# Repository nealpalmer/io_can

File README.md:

# IO_CAN
CAN GPIO device (4 GPIO pins, input, output, PWM, NeoPixel, 4x ADC, 2x DAC, 5V out, 6-25V in, CAN 1Mb/s)

This is a circuit boards to plug into the FRC can bus, and give you 4 GPIO pins for use in software.  This should help reduce the complexity of wiring, by putting the GPIO near the device.  There is probably already CAN and power near where the sensor would need to be.

# todo:
- Finish schematics
- Finish firmware
- Finish FRC Java library

# Features:
- CAN interface to RoboRio (1Mbit, CAN-FD mode not supported)
- Pass-through CAN pins on 2 connectors
- Latching connector for CAN and GPIO.
- 4 GPIO pins (each connector has 5V,GND,GPIO,GPIO).
- digital input/output on all 4 pins
- 10-bit ADC input on all 4 pins
- 8-bit DAC+OPAMP output on 2 pins
- AB decoder on 2 pins
- Neopixel output on 1 pin.  Supports 6 LED groups, and each group is a programmable number of LEDs.
- PWM output on all 4 pins (TBD)???
- PWM input measurement on all 4 pins (TBD)???
- 5V @ 1A output power
- 6V to 25V input voltage (very low current draw, except for 5V output power)
- Reverse voltage protection on CAN and GPIO connectors.
- Can be powered by USB or CAN connector (but don't do both, because it might back-power the USB port).

# RGB led
- One led is for CAN informaion {green flashing = working, red flashing = no valid can detected, blue flashing = running in match}
- One led for status of GPIO[0,1] {xor 0&1, ADC->brightness, AB decoder lsb, DAC->brightness, direct software control}
- one led for status of GPIO[2,3] {...}

# CAN messages
- Set RGB leds
- Set pin mode&value {input, output 0/1, pwm width/period, pwm measure, ADC value, DAC, neopixel group/RGB, ab decoder}
- Status of GPIO {GPIO[0] 16-bit, GPIO[1] 16-bit, GPIO[2] 16-bit, GPIO[3] 16-bit}.
- status: AB decoder uses 32 bits.
- status: PWM decoder reports 16-bit floating point
  
# NeoPixel
- Uses an off-the-shelf neopixel array (WS2812B 5V leds) [Strip_of_leds](https://www.amazon.com/dp/B09PBHJG6G) [ring_of_leds](https://www.amazon.com/dp/B08GPWVD57)
- Takes over GPIO#0
- You MUST pay attention to the current draw of the string.  The entire IO_CAN is limited to 1A, and if you draw much more than that, the fuse will blow, and everything will stop working.  So make sure that the length of string can't draw too much power.
- Possibly add an external power connection to power the neopixel array.
- Color choices:
  - 0x00-0x3f: Black-to-White solid color choices (4 values per R,G,B)
  - 0x80-0xff: Single white LED on (can be set to match the rotary encoder)
  - Rainbow
  - Moving Rainbow

# Files included:
- UsbJoy_d12_a4_r-rev2/: Kicad layout files, and gerbers
- SmartButton-rev2/: Kicad layout files, and gerbers
- UsbJoy_bill_of_materials.csv: spreadsheets with all of the parts to purchase and quantities and ordering links, pcb, buttons, cables, other stuff...
- mechanics/: openscad & STL files for a couple of mounts for UsbJoy using the SmartButton, rotary dial, 
- software/SmartButton_firmware/:
- software/UsbJoy_firmware/: firmware for the Atmega32U4 microcontroller
- software/UsbJoy_pic_firmware/: firmware 
- software/program_pic/: small application to program the pic16f1778 on UsbJoy, and pic15f15213 on SmartButton

# Manufacturing suggestions:
- [oshpark.com](https://oshpark.com/) has wonderful pricing for qty3 of 2and4 layer boards and ships in 10 calendar days for almost everything (and you can pay more to get it earlier, or pay for faster shipping)
  - [UsbJoy_R2](https://oshpark.com/shared_projects/QPZCB1ZT) board order $20/3 boards
  - [SmartButton_R2](https://oshpark.com/shared_projects/OV1uAkH7) board order $1.70/3 boards ($6.80/12 boards)
- A 3d-printer can make the UsbJoy board attach directly to the screw threads of one of the buttons.  A couple of sample mount's source files are [here](https://makerworld.com/en/models/1602536-usbjoy-controller-mount-30mm-arcade-button).
- An 3d printed [encoder spring](https://makerworld.com/en/models/1602721-rotary-encoder-rotary-friction-spring) makes the encoder much better for not spinning the robot wildly.
- An [acrylic wheel](https://makerworld.com/en/models/1605249-encoder-finger-wheel) with finger holes for the encoder is very useful.
- Testing for button functionality can be done in windows with the built-in "USB game controllers"->properties window to see the buttons that get pressed. NEED A PICTURE HERE!
- You can extract a 3d model of the boards from kicad to use in your 3d cad system.  Kicad: File->Export->STEP
- digikey has all of the electrical components necessary (except for the LED and Arduino board).
- 3x UsbJoy parts kit
- 12x SmartButton parts kit
- The arduino pro micro has a 0.5A fuse on it.  The bottom side of the board will NOT be accessible.  If that 0.5A fuse is on the bottom side, and you have over current, then your boards will not be salvageable.  So get a version that has all the components on the top side.
- The discrete components are 0603 packages for easier soldering.
- Get some [illuminated magnifying glasses](https://www.amazon.com/YOCTOSUN-Magnifying-Rechargeable-1-5X-3-5X-Magnifier/dp/B0D8J3TYL3) for ease of soldering of small components. 
- Solder all of the SMT components before any thru-hole components.  Required for both boards, because some of the thru-hole soldering will make SMT parts unreachable.

# How to program Arduino Pro Micro's Atmega32U4 (the USB device):
- Run the [Arduino GUI](https://www.arduino.cc/en/software/) version 1.8.19 (or newer than May 2025).
- Load the *.ino file
- Set up the board to be "Arduino Leonardo".
- Plug in the board into USB, then select the right Com port in the Arduino GUI.
- "Upload" 
 from the Arduino GUI.
- Programming does not clear the EEPROM, so any settings should remain unaffected.

# How to program pic16f1778 on UsbJoy using PICKIT5 programmer:
- Disconnect the last 2 buttons (Yellow and white next to each other)
- type "q1" on the uart to disable the 7,10,11 button communications
- Run the [Microchip IDE](https://www.microchip.com/en-us/tools-resources/develop/mplab-x-ide)
- Load the project
- Compile the project for production
- Use one of the current PIC programmers (pickit5 is probably preferred), and plug it into the 5-pin holes on the bottom side of the board.  And have the IDE program the device.
- type "q0" on the uart to re-enable the last 2 button functionality
# How to program pic16f1778 on UsbJoy using UsbJoy's USB connection:
- Disconnect buttons 7,10,11 (Green, White, Yellow) - they will interfere with the programming.
- Connect UsbJoy to the Windows PC.
- Figure out what com port (use Windows Device Manager) UsbJoy is using.
- Run "program_pic.exe usbjoy [filename].hex COM[#]"
- Press and hold the button next to the rotary connector for the full programming time (about 15 seconds).  If you forget this step, then you will receive a message "Error: couldn't find expected PIC CPU".
- Wait for programming to complete.
- Release the button.
- You can now reconnect the disconnected buttons.

# How to program pic16f15213 on SmartButton using PICKIT5:
- Run the [Microchip IDE](https://www.microchip.com/en-us/tools-resources/develop/mplab-x-ide)
- Load the project
- Compile the project for production
- Make sure the SmartButton isn't pressed, Connect the 3-pin cable to the UsbJoy (for 5V power), plug the pickit5 into the 5-pin holes on the SmartButton board.  And have the IDE program the device.
# How to program pic16f15213 on SmartButton using UsbJoy's USB interface:
- Connect 3+3+3pin cable ends into UsbJoy (match yellow J12,white J11,green J8 connectors), connect 5-pin cable end into SmartButton.
- Run "program_pic sb smartbutton.hex COM[#]".
- Quick Test: While plugged into the 5-pin cable, you should see the led in the button flicker VERY VERY dim.
- Quick Test: While plugged into the 5-pin cable, if you press the button, the LED should light up.
- You will need to create a cable to connect J8,J11,J12 to a 5-pin header.  It is probably easiest and more reliable to make an 3+3+3-pin to 5-pin XH only cable, and then solder the B5B-XH header to a 0.1" header.
 - pin1: MCLRn -> Red/Green/J8.2
 - pin2: 5V -> White/White/J11.1
 - pin3: GND -> Blue/Yellow/J12.3
 - pin4: PGD -> Blue/Yellow/J12.2
 - pin5: PGC -> White/White/J11.2
 - 
 - 

# How to initially configure UsbJoy:
- Connect USB to a PC.
- Open a terminal program (I like [MobaXterm](https://mobaxterm.mobatek.net/)), and connect to the correct com port (use windows device manager, and find the 'leonardo' port listed) (linux: 'dmesg' to find the correct '/dev/ttyUSB#' when you plug into USB).
- Any baud rate is fine, because it is a virtual serial port.
- 'h'+enter to get the help menu
- All settings commands are "letter+hex_number+enter".
- Important EEPROM settings to run:
  - 'u#" to set the upper 4 bits for the virtual buttons to uniquely identify this particular board (saved to EEPROM)
  - "m#val" to set the SmartLed DEFAULT setting for that port (not for the SmartLed itself) to the desired LED pattern (and toggle functionality) (saved to EEPROM)
  - "n#" to set the number of neopixel leds in the string - set to "n0" to indicate that there isn't a neopixel string.
  - "v#" to set the power-on setting for the Green ports - probably want them always on "vF" unless they are being used in some interesting way.
  - "V#" to set the power-on DEFAULT for the Green ports (saved to EEPROM)

# Future enhancements
- Add a 5-pin direct programming header for connecting to SmartButton (no need for weird programming cable).
- Move QR code to top side of board.

# History of major changes
- 8/8/2025: Added RZ axis to have the full resolution of the 2400/rev encoder when used with FRC DriverStation that only has 200 values per axis.
- 7/16/2025: Added MPLAB project files.
- 7/16/2025: SmartButton pic programming working over USB
- 7/16/2025: Added PDF of schematics.
- 7/15/2025: Uploaded 3d and lasercut objects to makerworld.com

Neal Palmer,
**FRC team #2984 Vikings Robotics,**
La Jolla, CA, USA

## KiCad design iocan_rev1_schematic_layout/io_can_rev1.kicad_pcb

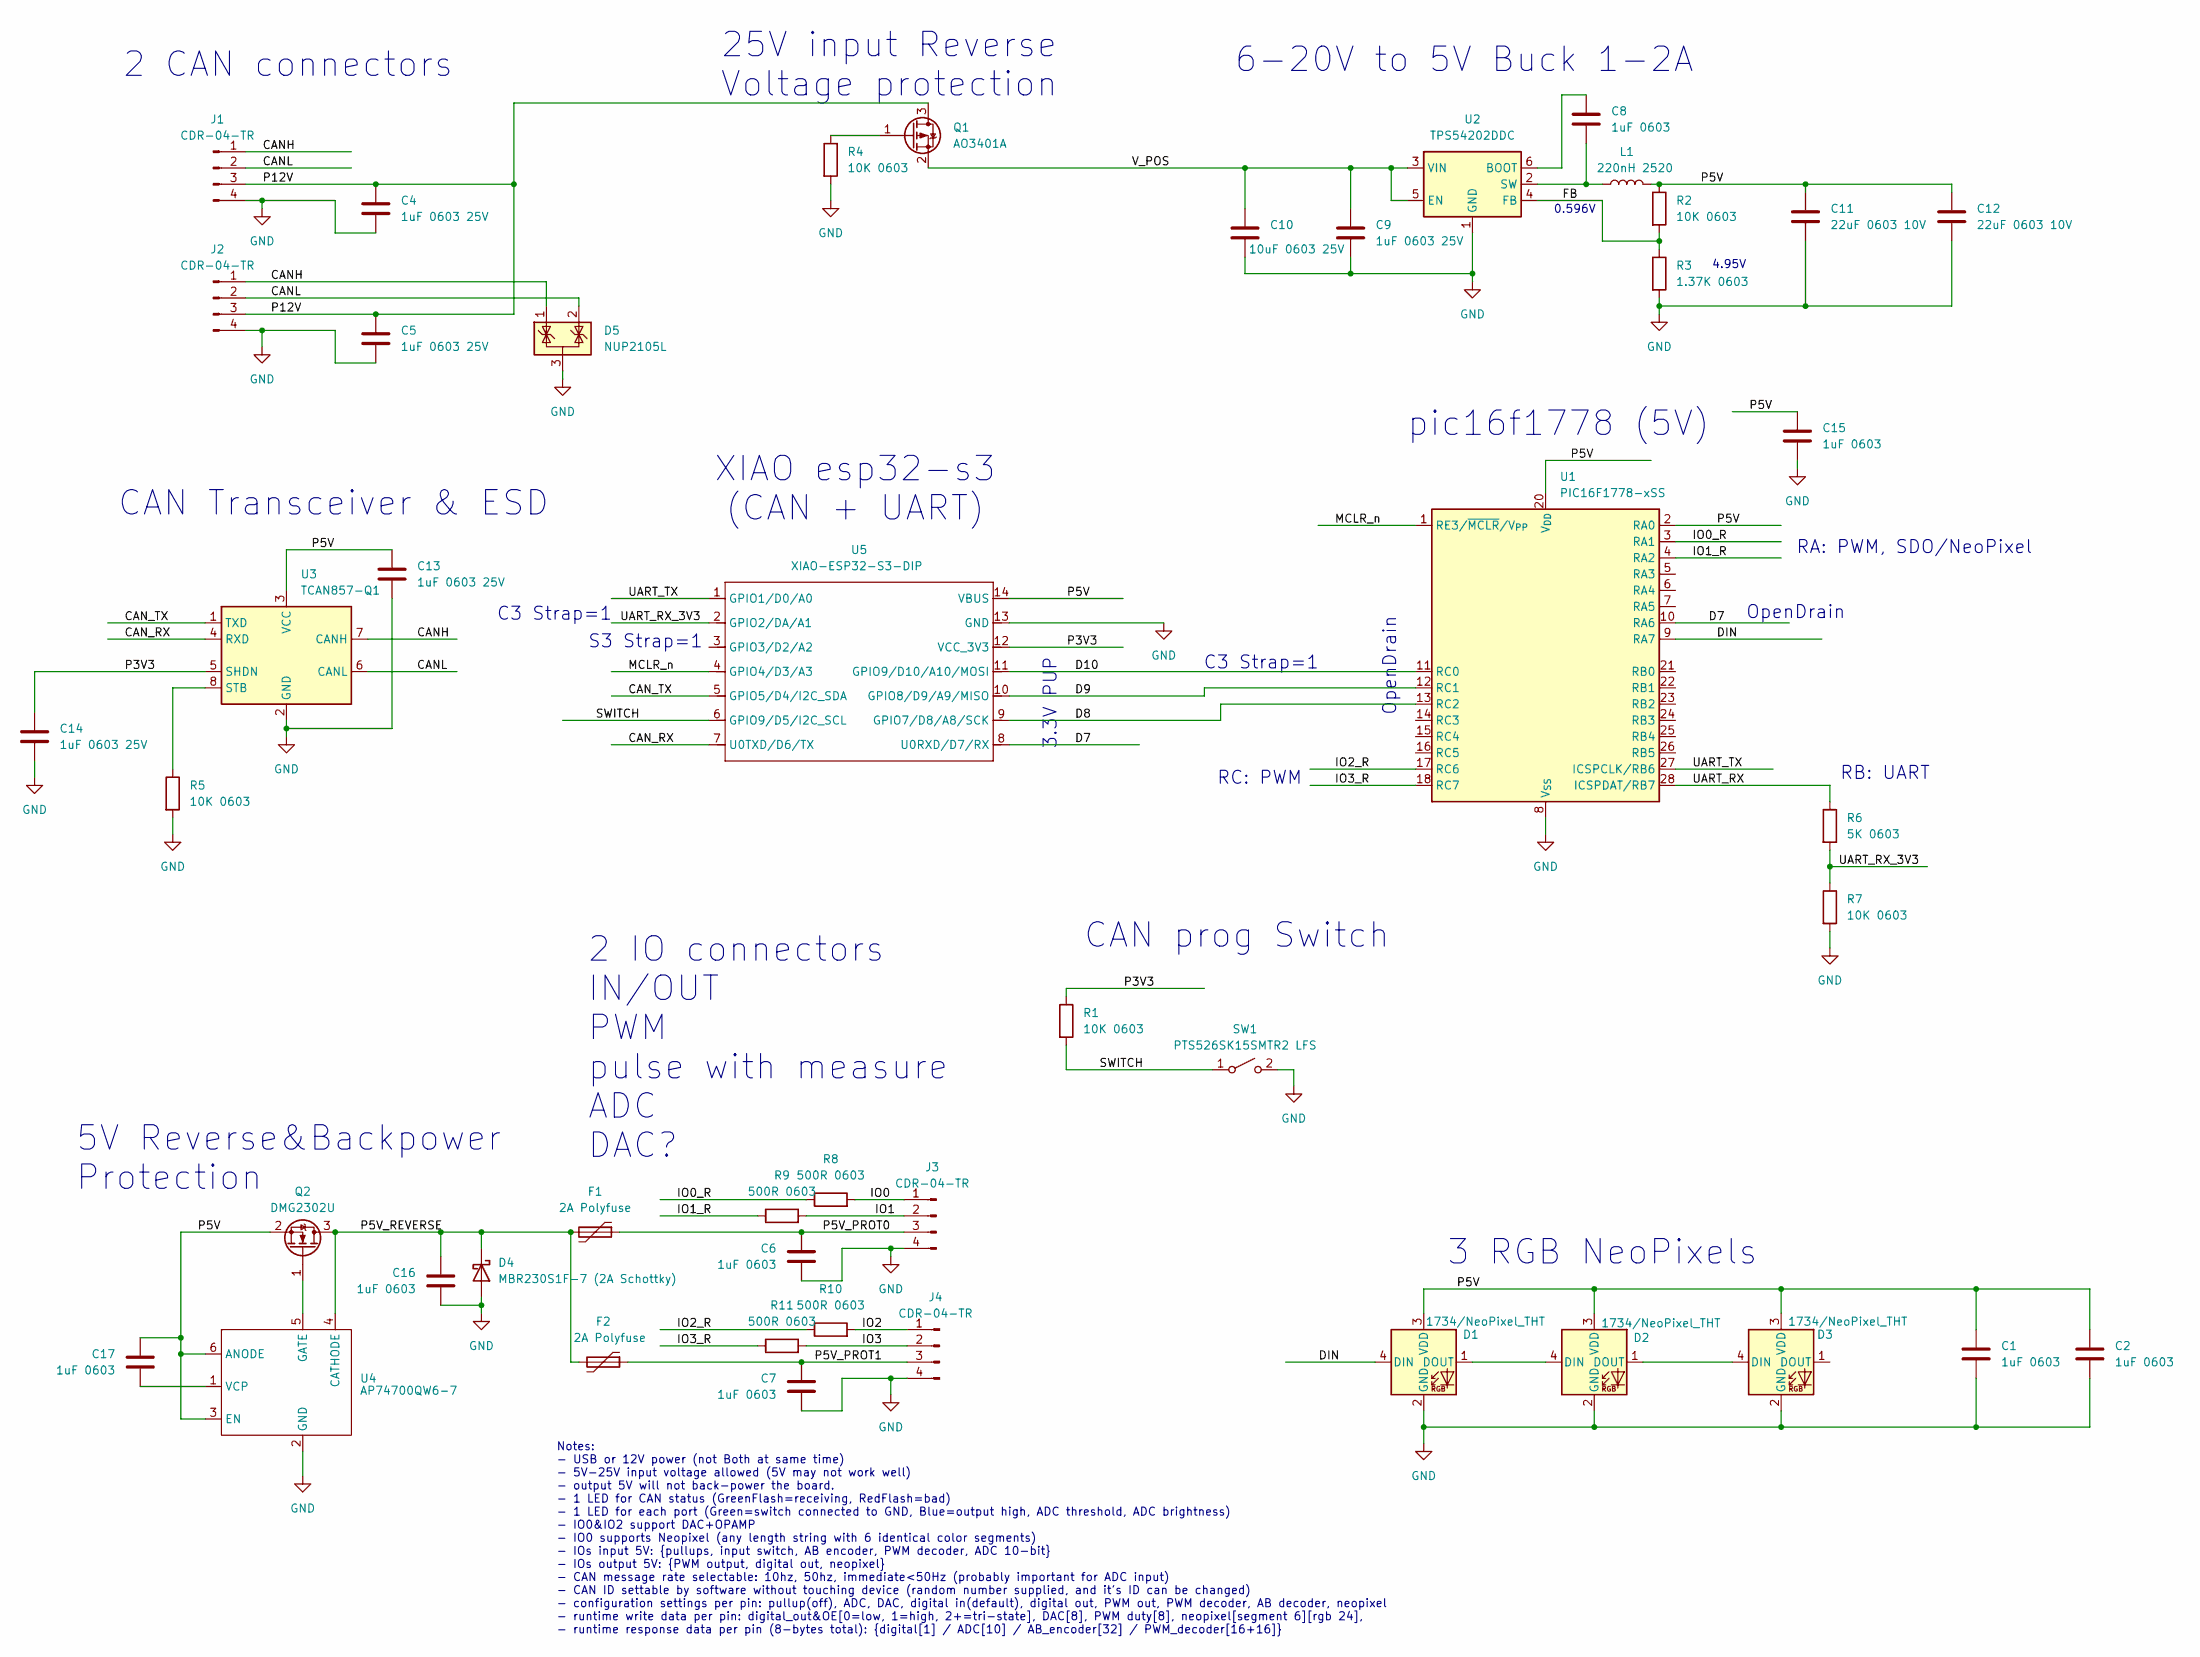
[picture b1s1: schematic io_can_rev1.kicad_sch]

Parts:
C1, C2, C6, C7, C8, C15, C16, C17: 1uF 0603; C_0603_1608Metric_Pad1.08x0.95mm_HandSolder
C4, C5, C9, C13, C14: 1uF 0603 25V; C_0603_1608Metric_Pad1.08x0.95mm_HandSolder
C10: 10uF 0603 25V; C_0603_1608Metric_Pad1.08x0.95mm_HandSolder
C11, C12: 22uF 0603 10V; C_0603_1608Metric_Pad1.08x0.95mm_HandSolder
D1, D2, D3: 1734/NeoPixel_THT; LED_D5.0mm-4_RGB_Staggered_Pins
D4: MBR230S1F-7 (2A Schottky); D_SOD-123F
D5: NUP2105L; SOT-23
F1, F2: 2A Polyfuse; Fuse_1206_3216Metric_Pad1.42x1.75mm_HandSolder
J1, J2, J3, J4: CDR-04-TR
L1: 220nH 2520; L_1008_2520Metric_Pad1.43x2.20mm_HandSolder
Q1: AO3401A; SOT-23
Q2: DMG2302U; SOT-23
R1, R2, R4, R5, R7: 10K 0603; R_0603_1608Metric_Pad0.98x0.95mm_HandSolder
R3: 1.37K 0603; R_0603_1608Metric_Pad0.98x0.95mm_HandSolder
R6: 5K 0603; R_0603_1608Metric_Pad0.98x0.95mm_HandSolder
R8, R9, R10, R11: 500R 0603; R_0603_1608Metric_Pad0.98x0.95mm_HandSolder
SW1: PTS526SK15SMTR2 LFS; SW_Tactile_SPST_NO_Straight_CK_PTS636Sx25SMTRLFS
U1: PIC16F1778-xSS; SSOP-28_5.3x10.2mm_P0.65mm
U2: TPS54202DDC; SOT-23-6
U3: TCAN857-Q1; TSOT-23-8_HandSoldering
U4: AP74700QW6-7; SOT-23-6_Handsoldering
U5: XIAO-ESP32-S3-DIP; XIAO-ESP32S3-DIP

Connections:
/CANH: D5.1 (K), J1.1, J2.1, U3.7 (CANH)
/CANL: D5.2 (K), J1.2, J2.2, U3.6 (CANL)
/CAN_RX: U3.4 (RXD), U5.7 (U0TXD/D6/TX)
/CAN_TX: U3.1 (TXD), U5.5 (GPIO5/D4/I2C_SDA)
/D7: U1.10 (RA6), U5.8 (U0RXD/D7/RX)
/D8: U1.13 (RC2), U5.9 (GPIO7/D8/A8/SCK)
/D9: U1.12 (RC1), U5.10 (GPIO8/D9/A9/MISO)
/D10: U1.11 (RC0), U5.11 (GPIO9/D10/A10/MOSI)
/DIN: D1.4 (DIN), U1.9 (RA7)
/FB: R2.2, R3.1, U2.4 (FB)
/IO0: J3.1, R8.2
/IO0_R: R8.1, U1.3 (RA1)
/IO1: J3.2, R9.2
/IO1_R: R9.1, U1.4 (RA2)
/IO2: J4.1, R10.2
/IO2_R: R10.1, U1.17 (RC6)
/IO3: J4.2, R11.2
/IO3_R: R11.1, U1.18 (RC7)
/MCLR_n: U1.1 (RE3/~MCLR/V_{PP}), U5.4 (GPIO4/D3/A3)
/P3V3: C14.1, R1.1, U3.5 (SHDN), U5.12 (VCC_3V3)
/P5V: C1.1, C2.1, C11.1, C12.1, C13.1, C15.1, C17.1, D1.3 (VDD), D2.3 (VDD), D3.3 (VDD), L1.2, Q2.2 (S), R2.1, U1.2 (RA0), U1.20 (V_{DD}), U3.3 (VCC), U4.3 (EN), U4.6 (ANODE), U5.14 (VBUS)
/P5V_PROT0: C6.1, F1.1, J3.3
/P5V_PROT1: C7.1, F2.1, J4.3
/P5V_REVERSE: C16.1, D4.1 (K), F1.2, F2.2, Q2.3 (D), U4.4 (CATHODE)
/P12V: C4.1, C5.1, J1.3, J2.3, Q1.3 (D)
/SWITCH: R1.2, SW1.1 (A), U5.6 (GPIO9/D5/I2C_SCL)
/UART_RX: R6.1, U1.28 (ICSPDAT/RB7)
/UART_RX_3V3: R6.2, R7.1, U5.2 (GPIO2/DA/A1)
/UART_TX: U1.27 (ICSPCLK/RB6), U5.1 (GPIO1/D0/A0)
/V_POS: C9.1, C10.1, Q1.2 (S), U2.3 (VIN), U2.5 (EN)
GND: C1.2, C2.2, C4.2, C5.2, C6.2, C7.2, C9.2, C10.2, C11.2, C12.2, C13.2, C14.2, C15.2, C16.2, D1.2 (GND), D2.2 (GND), D3.2 (GND), D4.2 (A), D5.3 (A), J1.4, J2.4, J3.4, J4.4, R3.2, R4.2, R5.2, R7.2, SW1.2 (B), U1.8 (V_{SS}), U1.19 (V_{SS}), U2.1 (GND), U3.2 (GND), U4.2 (GND), U5.13 (GND)
unnamed: D1.1 (DOUT), D2.4 (DIN)
unnamed: D2.1 (DOUT), D3.4 (DIN)
unnamed: Q1.1 (G), R4.1
unnamed: Q2.1 (G), U4.5 (GATE)
unnamed: C8.1, U2.6 (BOOT)
unnamed: C8.2, L1.1, U2.2 (SW)
unnamed: R5.1, U3.8 (STB)
unnamed: C17.2, U4.1 (VCP)

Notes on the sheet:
pic16f1778 (5V)
RA: PWM, SDO/NeoPixel
XIAO esp32-s3 (CAN + UART)
6-20V to 5V Buck 1-2A
4.95V
CAN Transceiver & ESD
RB: UART
C3 Strap=1
OpenDrain
2 IO connectors IN/OUT PWM pulse with measure ADC DAC?
CAN prog Switch
3.3V PUP
S3 Strap=1
0.596V
RC: PWM
5V Reverse&Backpower Protection
Notes: - USB or 12V power (not Both at same time) - 5V-25V input voltage allowed (5V may not work well) - output 5V will not back-power the board. - 1 LED for CAN status (GreenFlash=receiving, RedFlash=bad) - 1 LED for each port (Green=switch connected to GND, Blue=output high, ADC threshold, ADC b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
2 CAN connectors
25V input Reverse Voltage protection
3 RGB NeoPixels

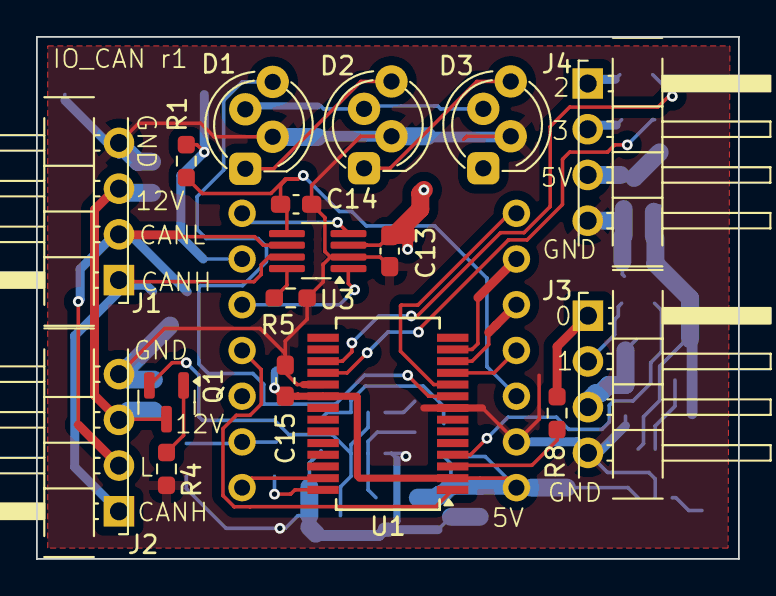
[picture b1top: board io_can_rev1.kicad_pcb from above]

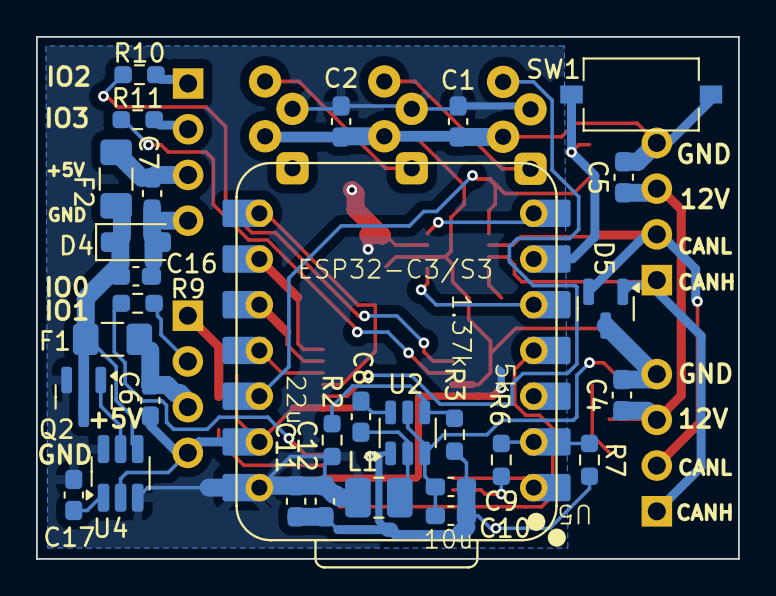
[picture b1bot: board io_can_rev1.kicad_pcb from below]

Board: 2 copper layers, 39.0 x 29.0 mm, 47 parts (30 on the bottom side), 39 nets.

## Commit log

2025-11-07 Added Kicad schematic and layout.
